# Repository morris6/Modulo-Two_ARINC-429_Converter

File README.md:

# Modulo-Two to ARINC-429 converter
Converting a Modulo-Two Serial Stream to Arinc-429 Serial Words.
### What's it for?
The Modulo-Two Serial Stream originates from a rather obsolete (around 1970 style) airborn High Frequency Communication Radio Control Panel.
This panel is installed in the cockpit and it controls a High Frequency Transceiver located in an aircrafts electronic compartment.
The panel is a Collins Controller 514A-4 and the transceiver a Collins HF Receiver Transmitter HFS-700.
### Why do we need one?
We want this panel to control a somewhat less obsolete High Frequency Communication Transceiver (1990 to 2010?) that requires Arinc-429 standard control signals.
### OK, show us.
The converter is an electronic device build in a box. Signals from the panel go in, and the output is routed to the transceiver. The device consists of an electronic circuit board and connectors. On this board a microcontroller works together with some support circuits to transform the incoming serial stream in Arinc-429 serial words.

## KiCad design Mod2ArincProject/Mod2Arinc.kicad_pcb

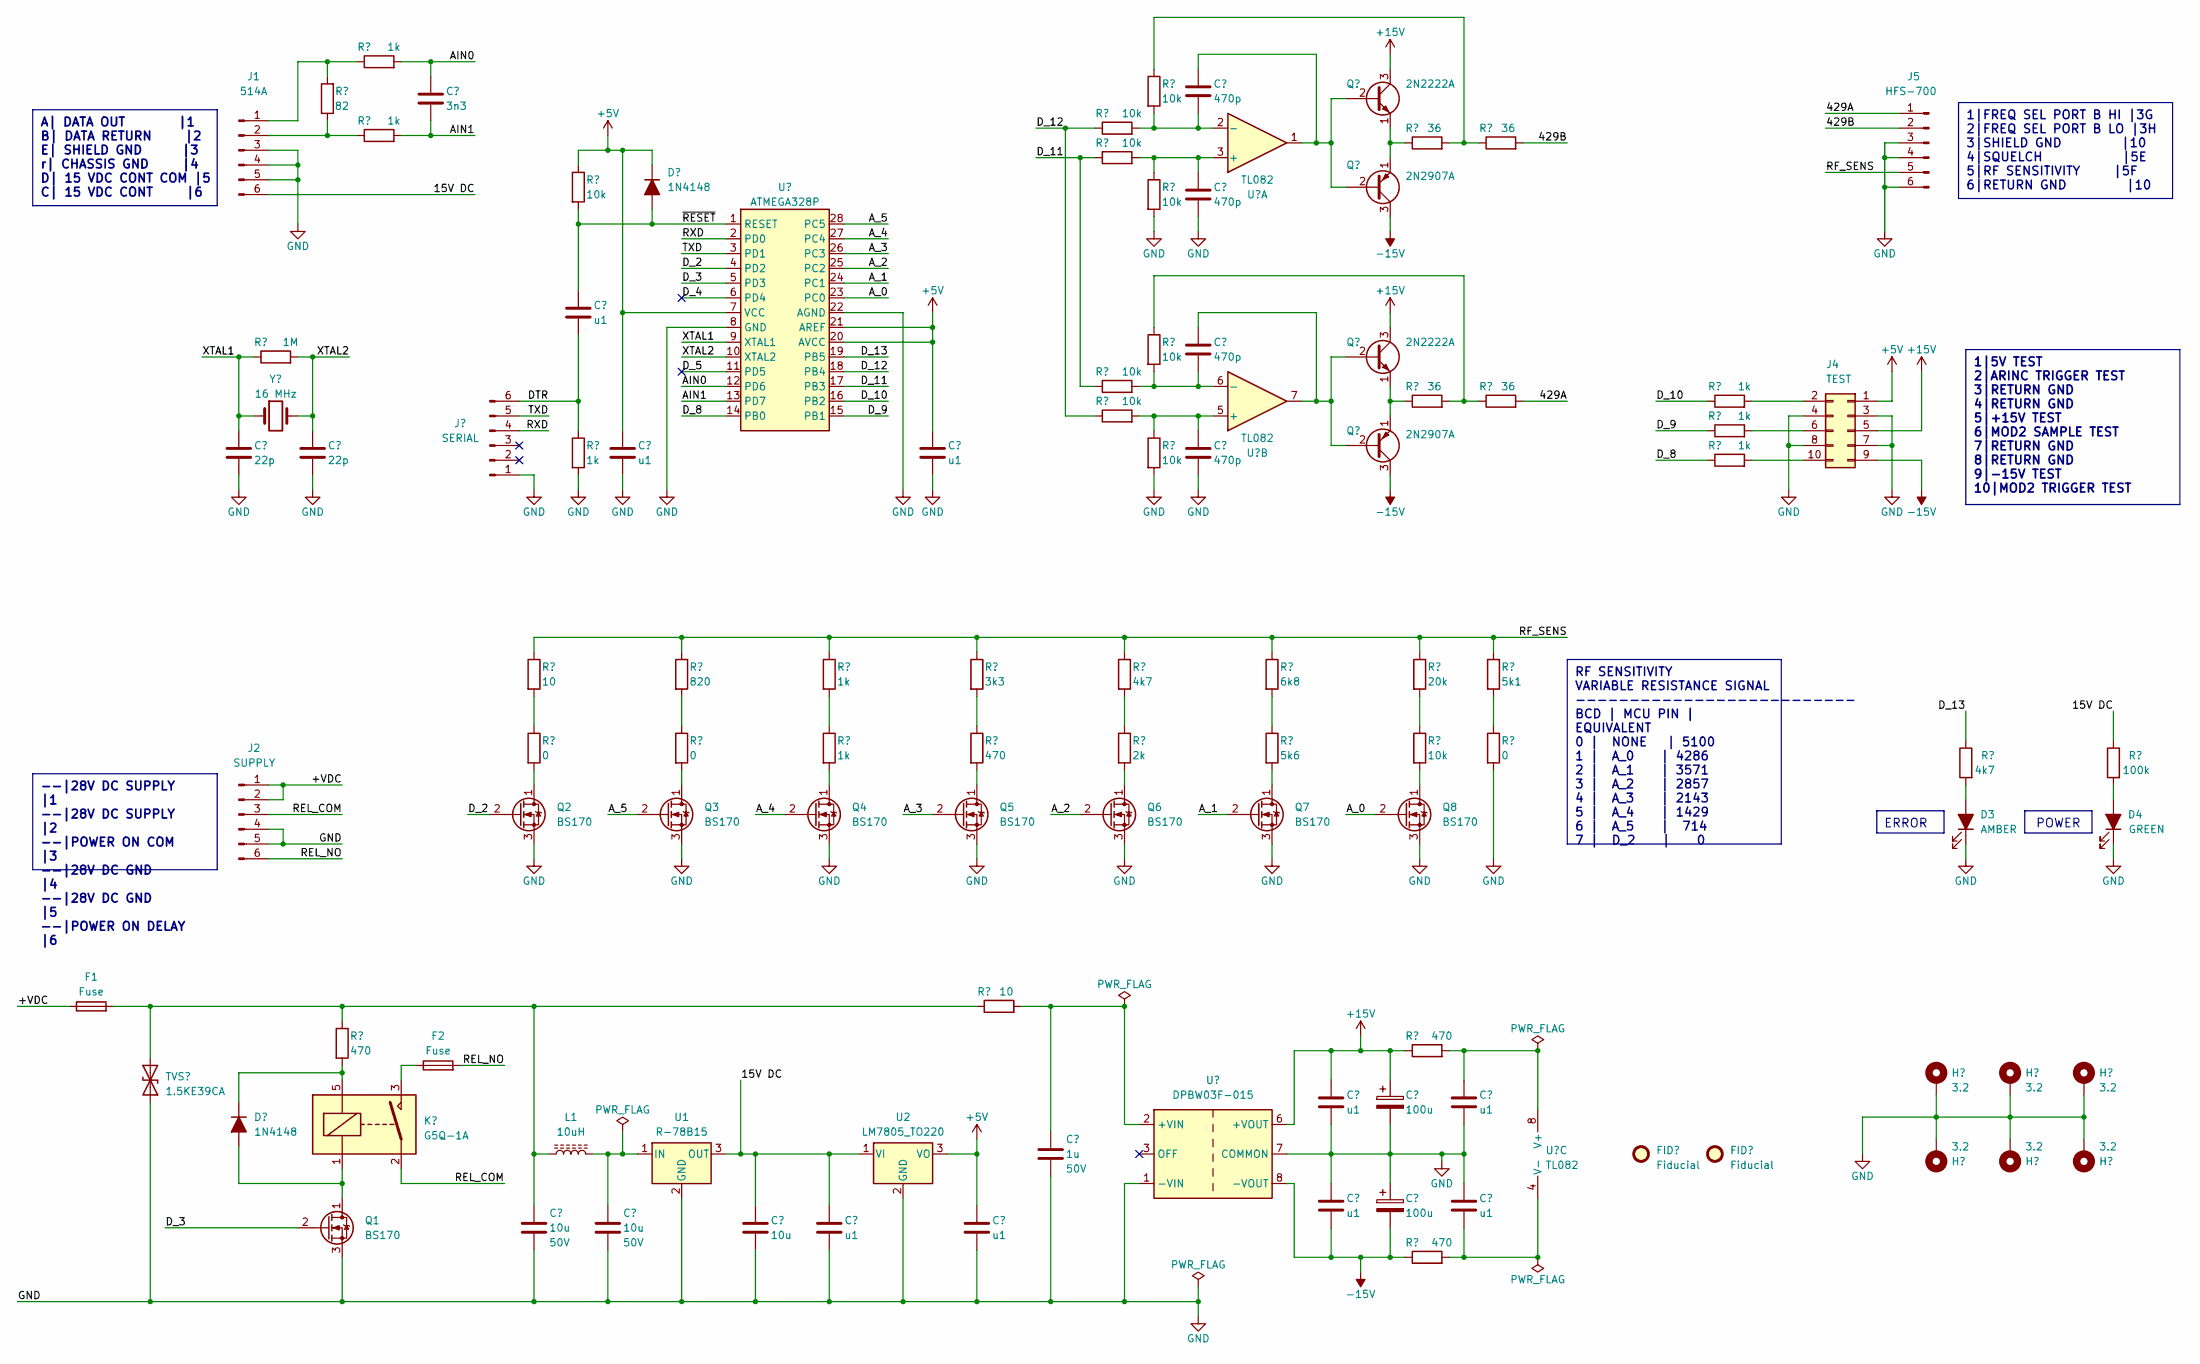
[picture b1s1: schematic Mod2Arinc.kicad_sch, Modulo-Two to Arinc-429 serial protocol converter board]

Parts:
C1, C2: 22p; C_Disc_D4.7mm_W2.5mm_P5.00mm
C3, C4, C7: 10u; C_Disc_D5.0mm_W2.5mm_P5.00mm
C5, C6, C8, C9, C11, C12, C13, C20, C21: u1; C_Disc_D3.8mm_W2.6mm_P2.50mm
C10: 1u; C_Disc_D5.0mm_W2.5mm_P5.00mm
C14, C15, C16, C17: 470p; C_Disc_D4.7mm_W2.5mm_P5.00mm
C18, C19: 100u; CP_Radial_D8.0mm_P3.80mm
C22: 3n3; C_Rect_L7.0mm_W2.5mm_P5.00mm
D1, D2: 1N4148; D_DO-35_SOD27_P10.16mm_Horizontal
D3: AMBER; LED_D5.0mm
D4: GREEN; LED_D5.0mm
F1, F2: Fuse; Fuseholder_Cylinder-5x20mm_Schurter_0031_8201_Horizontal_Op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
FID1, FID2: Fiducial; Fiducial_1mm_Mask2mm
H1, H2, H3, H4, H5, H6: 3.2; MountingHole_3.2mm_M3_Pad_TopBottom
J1: 514A; PhoenixContact_MCV_1,5_6-G-3.81_1x06_P3.81mm_Vertical
J2: SUPPLY; PhoenixContact_MCV_1,5_6-G-3.81_1x06_P3.81mm_Vertical
J3: SERIAL; PinHeader_1x06_P2.54mm_Vertical
J4: TEST; PinSocket_2x05_P2.54mm_Vertical
J5: HFS-700; PhoenixContact_MCV_1,5_6-G-3.81_1x06_P3.81mm_Vertical
K1: G5Q-1A; Relay_SPST_Omron-G5Q-1A
L1: 10uH; L_Radial_D7.5mm_P3.50mm_Fastron_07P
Q1, Q2, Q3, Q4, Q5, Q6, Q7, Q8: BS170; TO-92L_Inline_Wide
Q9, Q11: 2N2222A; TO-92L_Inline_Wide
Q10, Q12: 2N2907A; TO-92L_Inline_Wide
R2, R25, R26, R74: 470; R_Axial_DIN0207_L6.3mm_D2.5mm_P10.16mm_Horizontal
R3: 1M; R_Axial_DIN0207_L6.3mm_D2.5mm_P10.16mm_Horizontal
R4: 82; R_Axial_DIN0207_L6.3mm_D2.5mm_P10.16mm_Horizontal
R5, R6, R10, R11, R33, R34, R35, R73: 1k; R_Axial_DIN0207_L6.3mm_D2.5mm_P10.16mm_Horizontal
R7, R13: 10; R_Axial_DIN0207_L6.3mm_D2.5mm_P10.16mm_Horizontal
R8: 820; R_Axial_DIN0207_L6.3mm_D2.5mm_P10.16mm_Horizontal
R9, R16, R17, R18, R19, R21, R22, R23, R24, R77: 10k; R_Axial_DIN0207_L6.3mm_D2.5mm_P10.16mm_Horizontal
R12: 3k3; R_Axial_DIN0207_L6.3mm_D2.5mm_P10.16mm_Horizontal
R15, R36: 4k7; R_Axial_DIN0207_L6.3mm_D2.5mm_P10.16mm_Horizontal
R20: 6k8; R_Axial_DIN0207_L6.3mm_D2.5mm_P10.16mm_Horizontal
R27: 20k; R_Axial_DIN0207_L6.3mm_D2.5mm_P10.16mm_Horizontal
R28: 5k1; R_Axial_DIN0207_L6.3mm_D2.5mm_P10.16mm_Horizontal
R29, R30, R31, R32: 36; R_Axial_DIN0207_L6.3mm_D2.5mm_P10.16mm_Horizontal
R37: 100k; R_Axial_DIN0207_L6.3mm_D2.5mm_P10.16mm_Horizontal
R71, R72, R78: 0; R_Axial_DIN0207_L6.3mm_D2.5mm_P10.16mm_Horizontal
R75: 2k; R_Axial_DIN0207_L6.3mm_D2.5mm_P10.16mm_Horizontal
R76: 5k6; R_Axial_DIN0207_L6.3mm_D2.5mm_P10.16mm_Horizontal
TVS1: 1.5KE39CA; D_DO-201AD_P12.70mm_Horizontal
U1: R-78B15; Converter_DCDC_RECOM_R-78B-2.0_THT
U2: LM7805_TO220; TO-220-3_Horizontal_TabDown
U3: ATMEGA328P; DIP-28_W7.62mm_Socket
U4: DPBW03F-015; Converter_DCDC_TRACO_TMR-xxxx_THT
U5: TL082; DIP-8_W7.62mm
Y1: 16 MHz; Crystal_HC18-U_Vertical

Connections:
+5V: C6.1, C9.1, C11.1, D2.1 (K), J4.1, R9.1, U2.3 (VO), U3.7 (VCC), U3.20 (AVCC), U3.21 (AREF)
+15V: C12.1, C18.1, J4.5, Q9.3 (C), Q11.3 (C), R25.1, U4.6 (+VOUT)
-15V: C13.2, C19.2, J4.9, Q10.3 (C), Q12.3 (C), R26.1, U4.8 (-VOUT)
/15V DC: C7.1, C8.1, J1.6, R37.1, U1.3 (OUT), U2.1 (VI)
/429A: J5.1, R32.2
/429B: J5.2, R31.2
/+VDC: F1.1, J2.1, J2.2
/AIN0: C22.1, R6.2, U3.12 (PD6)
/AIN1: C22.2, R5.2, U3.13 (PD7)
/A_0: Q8.2 (G), U3.23 (PC0)
/A_1: Q7.2 (G), U3.24 (PC1)
/A_2: Q6.2 (G), U3.25 (PC2)
/A_3: Q5.2 (G), U3.26 (PC3)
/A_4: Q4.2 (G), U3.27 (PC4)
/A_5: Q3.2 (G), U3.28 (PC5)
/DTR: C5.2, J3.6, R10.1
/D_2: Q2.2 (G), U3.4 (PD2)
/D_3: Q1.2 (G), U3.5 (PD3)
/D_4: U3.6 (PD4)
/D_5: U3.11 (PD5)
/D_8: R35.1, U3.14 (PB0)
/D_9: R34.1, U3.15 (PB1)
/D_10: R33.1, U3.16 (PB2)
/D_11: R17.1, R18.1, U3.17 (PB3)
/D_12: R16.1, R19.1, U3.18 (PB4)
/D_13: R36.1, U3.19 (PB5)
/REL_COM: J2.3, K1.2
/REL_NO: F2.2, J2.6
/RF_SENS: J5.5, R7.1, R8.1, R11.1, R12.1, R15.1, R20.1, R27.1, R28.1
/RXD: J3.4, U3.2 (PD0)
/TXD: J3.5, U3.3 (PD1)
/XTAL1: C1.1, R3.1, U3.9 (XTAL1), Y1.1
/XTAL2: C2.1, R3.2, U3.10 (XTAL2), Y1.2
/~RESET: C5.1, D2.2 (A), R9.2, U3.1 (RESET)
GND: C1.2, C2.2, C3.2, C4.2, C6.2, C7.2, C8.2, C9.2, C10.2, C11.2, C12.2, C13.1, C15.2, C17.2, C18.2, C19.1, C20.2, C21.1, D3.1 (K), D4.1 (K), H1.1, H2.1, H3.1, H4.1, H5.1, H6.1, J1.3, J1.4, J1.5, J2.4, J2.5, J3.1, J4.3, J4.4, J4.7, J4.8, J5.3, J5.4, J5.6, Q1.3 (S), Q2.3 (S), Q3.3 (S), Q4.3 (S), Q5.3 (S), Q6.3 (S), Q7.3 (S), Q8.3 (S), R10.2, R22.2, R24.2, R78.2, TVS1.1 (A1), U1.2 (GND), U2.2 (GND), U3.8 (GND), U3.22 (AGND), U4.1 (-VIN), U4.7 (COMMON)
unnamed: D1.2 (A), K1.1, Q1.1 (D)
unnamed: D1.1 (K), K1.5, R2.2
unnamed: D3.2 (A), R36.2
unnamed: D4.2 (A), R37.2
unnamed: F2.1, K1.3
unnamed: J1.1, R4.2, R6.1
unnamed: J1.2, R4.1, R5.1
unnamed: J4.2, R33.2
unnamed: J4.6, R34.2
unnamed: J4.10, R35.2
unnamed: Q2.1 (D), R71.2
unnamed: Q3.1 (D), R72.2
unnamed: Q4.1 (D), R73.2
unnamed: Q5.1 (D), R74.2
unnamed: Q6.1 (D), R75.2
unnamed: Q7.1 (D), R76.2
unnamed: Q8.1 (D), R77.2
unnamed: C14.1, Q9.2 (B), Q10.2 (B), U5.1
unnamed: Q9.1 (E), Q10.1 (E), R29.1
unnamed: C16.1, Q11.2 (B), Q12.2 (B), U5.7
unnamed: Q11.1 (E), Q12.1 (E), R30.1
unnamed: R7.2, R71.1
unnamed: R11.2, R73.1
unnamed: R12.2, R74.1
unnamed: R15.2, R75.1
unnamed: R20.2, R76.1
unnamed: R21.1, R29.2, R31.1
unnamed: R23.1, R30.2, R32.1
unnamed: R27.2, R77.1
unnamed: R28.2, R78.1
unnamed: R8.2, R72.1
unnamed: C3.1, F1.2, L1.1, R2.1, R13.1, TVS1.2 (A2)
unnamed: C4.1, L1.2, U1.1 (IN)
unnamed: C10.1, R13.2, U4.2 (+VIN)
unnamed: C15.1, R17.2, R22.1, U5.3 (+)
unnamed: C14.2, R16.2, R21.2, U5.2 (-)
unnamed: C17.1, R19.2, R24.1, U5.5 (+)
unnamed: C16.2, R18.2, R23.2, U5.6 (-)
unnamed: C20.1, R25.2, U5.8 (V+)
unnamed: C21.2, R26.2, U5.4 (V-)

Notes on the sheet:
1|FREQ SEL PORT B HI |3G 2|FREQ SEL PORT B LO |3H 3|SHIELD GND |10 4|SQUELCH |5E 5|RF SENSITIVITY |5F 6|RETURN GND |10
1|5V TEST 2|ARINC TRIGGER TEST 3|RETURN GND 4|RETURN GND 5|+15V TEST 6|MOD2 SAMPLE TEST 7|RETURN GND 8|RETURN GND 9|-15V TEST 10|MOD2 TRIGGER TEST
A| DATA OUT |1 B| DATA RETURN |2 E| SHIELD GND |3 r| CHASSIS GND |4 D| 15 VDC CONT COM |5 C| 15 VDC CONT |6
ERROR
POWER
RF SENSITIVITY VARIABLE RESISTANCE SIGNAL -------------------------- BCD | MCU PIN | EQUIVALENT 0 | NONE | 5100 1 | A_0 | 4286 2 | A_1 | 3571 3 | A_2 | 2857 4 | A_3 | 2143 5 | A_4 | 1429 6 | A_5 | 714 7 | D_2 | 0
--|28V DC SUPPLY |1 --|28V DC SUPPLY |2 --|POWER ON COM |3 --|28V DC GND |4 --|28V DC GND |5 --|POWER ON DELAY |6

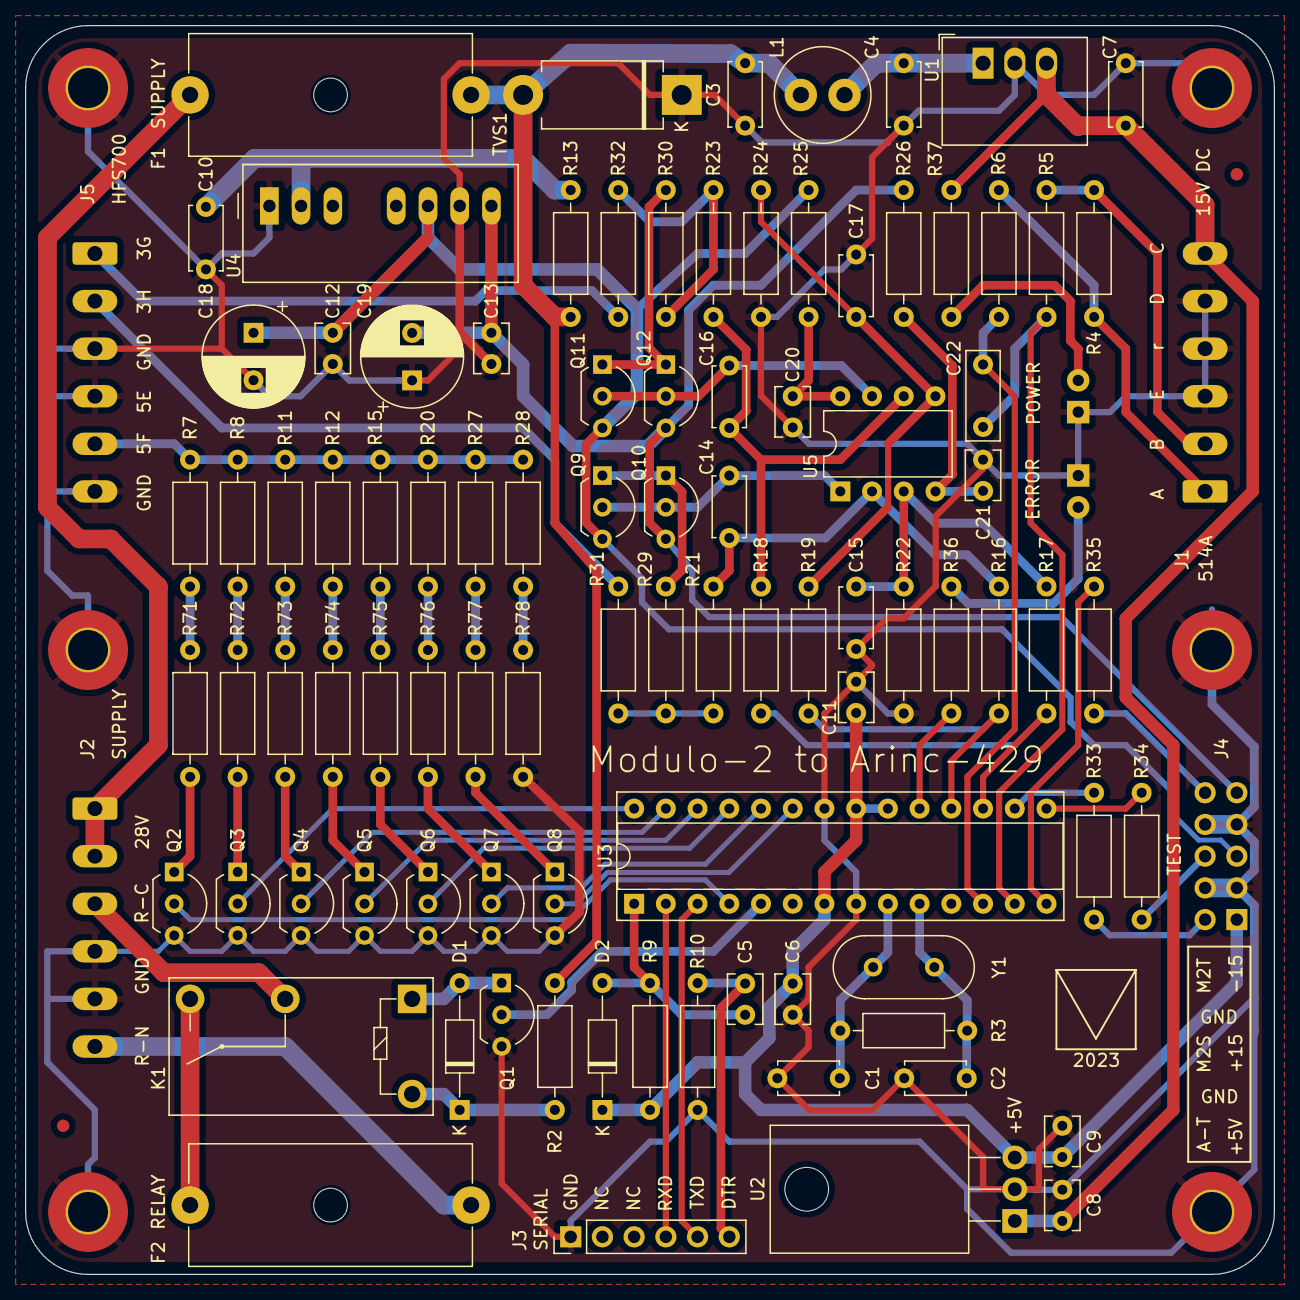
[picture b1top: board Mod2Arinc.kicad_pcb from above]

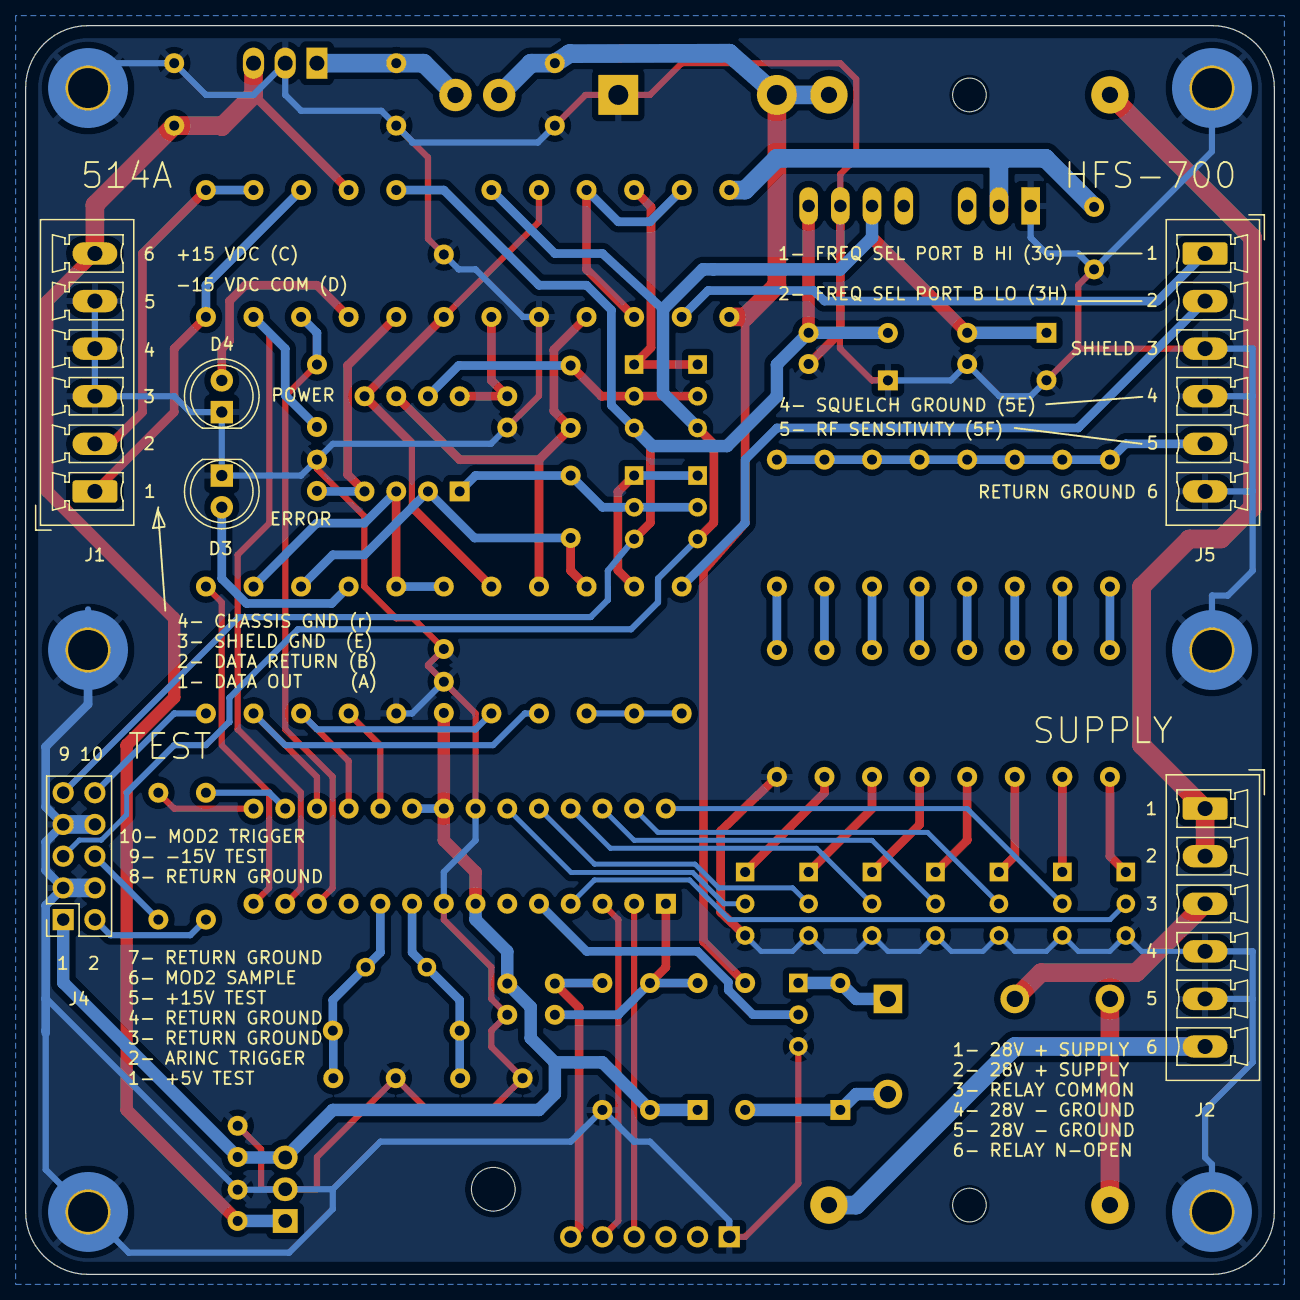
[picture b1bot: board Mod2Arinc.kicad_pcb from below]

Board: 2 copper layers, 100.0 x 100.0 mm, 105 parts (6 on the bottom side), 73 nets.

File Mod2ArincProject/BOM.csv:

Source:,C:\MyProjects\_HFS700\Mod2Arinc\Mod2ArincProject\Mod2Arinc.kicad_sch,,,,,,,,,
Date:,12/11/2023 20:13,,,,,,,,,
Tool:,Eeschema 7.0.7,,,,,,,,,
Generator:,C:\Program Files\KiCad\7.0\bin\scripting\plugins/bom_csv_grouped_by_value.py,,,,,,,,,
Component Count:,104,,,,,,,,,
,,,,,,,,,,
Collated Components:,,,,,,,,,,
,,,,,,,,,,
Item,Qty,Reference(s),Value,LibPart,Footprint,Datasheet,DNP,Field4,Sim.Device,Sim.Pins
1,2,"C1, C2",22p,Device:C,Capacitor_THT:C_Disc_D4.7mm_W2.5mm_P5.00mm,~,,,,
2,3,"C3, C4, C7",10u,Device:C,Capacitor_THT:C_Disc_D5.0mm_W2.5mm_P5.00mm,~,,50V,,
3,9,"C5, C6, C8, C9, C11, C12, C13, C20, C21",u1,Device:C,Capacitor_THT:C_Disc_D3.8mm_W2.6mm_P2.50mm,~,,,,
4,1,C10,1u,Device:C,Capacitor_THT:C_Disc_D5.0mm_W2.5mm_P5.00mm,~,,50V,,
5,4,"C14, C15, C16, C17",470p,Device:C,Capacitor_THT:C_Disc_D4.7mm_W2.5mm_P5.00mm,~,,,,
6,2,"C18, C19",100u,Device:C_Polarized,Capacitor_THT:CP_Radial_D8.0mm_P3.80mm,~,,,,
7,2,"D1, D2",1N4148,Device:D_Filled,Diode_THT:D_DO-35_SOD27_P10.16mm_Horizontal,~,,,D,1=K 2=A
8,1,D3,AMBER,Device:LED_Filled,LED_THT:LED_D5.0mm,~,,,,
9,1,D4,GREEN,Device:LED_Filled,LED_THT:LED_D5.0mm,~,,,,
10,2,"F1, F2",Fuse,Device:Fuse,Fuse:Fuseholder_Cylinder-5x20mm_Schurter_0031_8201_Horizontal_Open,~,,,,
11,2,"FID1, FID2",Fiducial,Mechanical:Fiducial,Fiducial:Fiducial_1mm_Mask2mm,~,,,,
12,6,"H1, H2, H3, H4, H5, H6",3.2,Mechanical:MountingHole_Pad,MountingHole:MountingHole_3.2mm_M3_Pad_TopBottom,~,,,,
13,1,J1,514A,Connector:Conn_01x06_Pin,"Connector_Phoenix_MC:PhoenixContact_MCV_1,5_6-G-3.81_1x06_P3.81mm_Vertical",~,,,,
14,1,J2,SUPPLY,Connector:Conn_01x06_Pin,"Connector_Phoenix_MC:PhoenixContact_MCV_1,5_6-G-3.81_1x06_P3.81mm_Vertical",~,,,,
15,1,J3,SERIAL,Connector:Conn_01x06_Pin,Connector_PinHeader_2.54mm:PinHeader_1x06_P2.54mm_Vertical,~,,,,
16,1,J4,TEST,Connector_Generic:Conn_02x05_Odd_Even,Connector_PinSocket_2.54mm:PinSocket_2x05_P2.54mm_Vertical,~,,,,
17,1,J5,HFS-700,Connector:Conn_01x06_Pin,"Connector_Phoenix_MC:PhoenixContact_MCV_1,5_6-G-3.81_1x06_P3.81mm_Vertical",~,,,,
18,1,K1,G5Q-1A,Relay:G5Q-1A,Relay_THT:Relay_SPST_Omron-G5Q-1A,https://www.omron.com/ecb/products/pdf/en-g5q.pdf,,,,
19,1,L1,10uH,Device:L_Ferrite,Inductor_THT:L_Radial_D7.5mm_P3.50mm_Fastron_07P,~,,,,
20,8,"Q1, Q2, Q3, Q4, Q5, Q6, Q7, Q8",BS170,Transistor_FET:BS170,Package_TO_SOT_THT:TO-92L_Inline_Wide,https://www.onsemi.com/pub/Collateral/BS170-D.PDF,,,,
21,2,"Q9, Q11",2N2222A,Device:Q_NPN_EBC,Package_TO_SOT_THT:TO-92L_Inline_Wide,~,,,,
22,2,"Q10, Q12",2N2907A,Device:Q_PNP_EBC,Package_TO_SOT_THT:TO-92L_Inline_Wide,~,,,,
23,6,"R2, R25, R26, R36, R37, R74",470,Device:R,Resistor_THT:R_Axial_DIN0207_L6.3mm_D2.5mm_P10.16mm_Horizontal,~,,,,
24,1,R3,1M,Device:R,Resistor_THT:R_Axial_DIN0207_L6.3mm_D2.5mm_P10.16mm_Horizontal,~,,,,
25,1,R4,82,Device:R,Resistor_THT:R_Axial_DIN0207_L6.3mm_D2.5mm_P10.16mm_Horizontal,~,,,,
26,8,"R5, R6, R10, R11, R33, R34, R35, R73",1k,Device:R,Resistor_THT:R_Axial_DIN0207_L6.3mm_D2.5mm_P10.16mm_Horizontal,~,,,,
27,2,"R7, R13",10,Device:R,Resistor_THT:R_Axial_DIN0207_L6.3mm_D2.5mm_P10.16mm_Horizontal,~,,,,
28,1,R8,820,Device:R,Resistor_THT:R_Axial_DIN0207_L6.3mm_D2.5mm_P10.16mm_Horizontal,~,,,,
29,9,"R9, R16, R17, R18, R19, R21, R22, R23, R24",10k,Device:R,Resistor_THT:R_Axial_DIN0207_L6.3mm_D2.5mm_P10.16mm_Horizontal,~,,,,
30,1,R12,3k3,Device:R,Resistor_THT:R_Axial_DIN0207_L6.3mm_D2.5mm_P10.16mm_Horizontal,~,,,,
31,1,R15,5k6,Device:R,Resistor_THT:R_Axial_DIN0207_L6.3mm_D2.5mm_P10.16mm_Horizontal,~,,,,
32,2,"R20, R77",12k,Device:R,Resistor_THT:R_Axial_DIN0207_L6.3mm_D2.5mm_P10.16mm_Horizontal,~,,,,
33,1,R27,18k,Device:R,Resistor_THT:R_Axial_DIN0207_L6.3mm_D2.5mm_P10.16mm_Horizontal,~,,,,
34,1,R28,4k7,Device:R,Resistor_THT:R_Axial_DIN0207_L6.3mm_D2.5mm_P10.16mm_Horizontal,~,,,,
35,4,"R29, R30, R31, R32",36,Device:R,Resistor_THT:R_Axial_DIN0207_L6.3mm_D2.5mm_P10.16mm_Horizontal,~,,,,
36,3,"R71, R72, R75",0,Device:R,Resistor_THT:R_Axial_DIN0207_L6.3mm_D2.5mm_P10.16mm_Horizontal,~,,,,
37,1,R76,390,Device:R,Resistor_THT:R_Axial_DIN0207_L6.3mm_D2.5mm_P10.16mm_Horizontal,~,,,,
38,1,R78,270,Device:R,Resistor_THT:R_Axial_DIN0207_L6.3mm_D2.5mm_P10.16mm_Horizontal,~,,,,
39,1,TVS1,1.5KE39CA,Diode:1.5KExxCA,Diode_THT:D_DO-201AD_P12.70mm_Horizontal,https://www.vishay.com/docs/88301/15ke.pdf,,,,
40,1,U1,R-78B15,Regulator_Linear:L7815,Converter_DCDC:Converter_DCDC_RECOM_R-78B-2.0_THT,http://www.st.com/content/ccc/resource/technical/document/da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,,,,
41,1,U2,LM7805_TO220,Regulator_Linear:LM7805_TO220,Package_TO_SOT_THT:TO-220-3_Vertical,https://www.onsemi.cn/PowerSolutions/document/MC7800-D.PDF,,,,
42,1,U3,ATMEGA328P,_Emavec:ATMEGA328P,Package_DIP:DIP-28_W7.62mm_Socket,,,,,
43,1,U4,DPBW03F-015,_Emavec:DPBW06F,Converter_DCDC:Converter_DCDC_TRACO_TMR-xxxx_THT,https://www.tracopower.com/products/tmr2.pdf,,,,
44,1,U5,TL082,Amplifier_Operational:TL082,Package_DIP:DIP-8_W7.62mm,http://www.ti.com/lit/ds/symlink/tl081.pdf,,,,
45,1,Y1,16 MHz,Device:Crystal,Crystal:Crystal_HC18-U_Vertical,~,,,,
